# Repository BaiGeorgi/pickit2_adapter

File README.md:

# pickit2_adapter
PICkit2 AVR/Flashrom (SPI) adapter

https://hackaday.io/project/175148-pickit2-to-avrflashrom-spi-adapter

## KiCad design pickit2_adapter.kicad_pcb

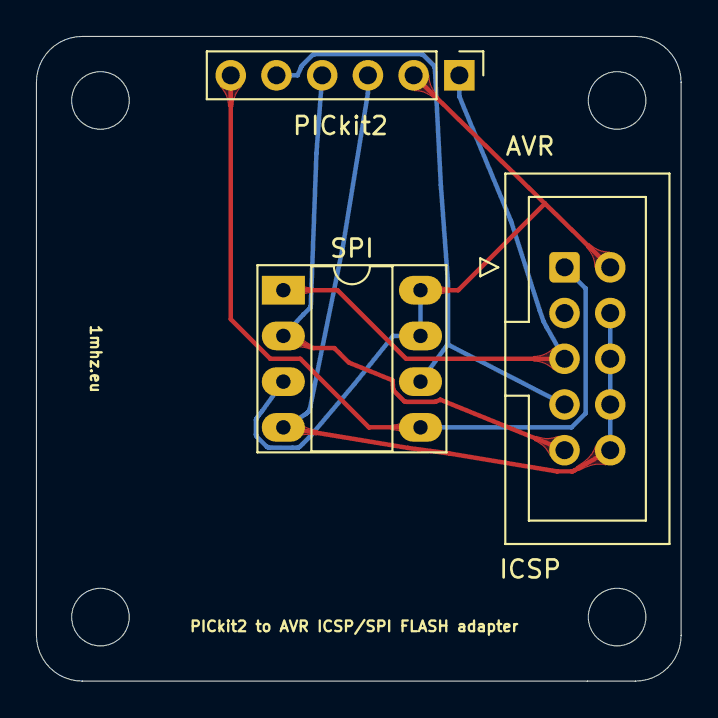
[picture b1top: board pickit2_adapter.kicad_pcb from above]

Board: 2 copper layers, 35.8 x 35.8 mm, 7 parts (0 on the bottom side), 6 nets.

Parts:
AVR: AVR ISP; IDC-Header_2x05_P2.54mm_Vertical
PICkit2: Conn_PIC_ICSP_ICD; PinHeader_1x06_P2.54mm_Vertical
R1, R2, R3, R4: MountingHole_3.2mm_M3
SPI: Conn_02x04_Top_Bottom; DIP-8_W7.62mm_Socket_LongPads

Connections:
GND: AVR.4, AVR.6, AVR.8, AVR.10, PICkit2.3, SPI.4
VDD: AVR.2, PICkit2.2, SPI.3, SPI.7, SPI.8
pgc: AVR.7, PICkit2.5, SPI.6
pgd: AVR.9, PICkit2.4, SPI.2
pgm: AVR.1, PICkit2.6, SPI.5
vpp: AVR.5, PICkit2.1, SPI.1

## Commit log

2020-10-02 Removed images
2020-10-02 Updated license
2020-10-08 Fixed mask
2020-11-13 Update README.md
    Added hackaday.io url
